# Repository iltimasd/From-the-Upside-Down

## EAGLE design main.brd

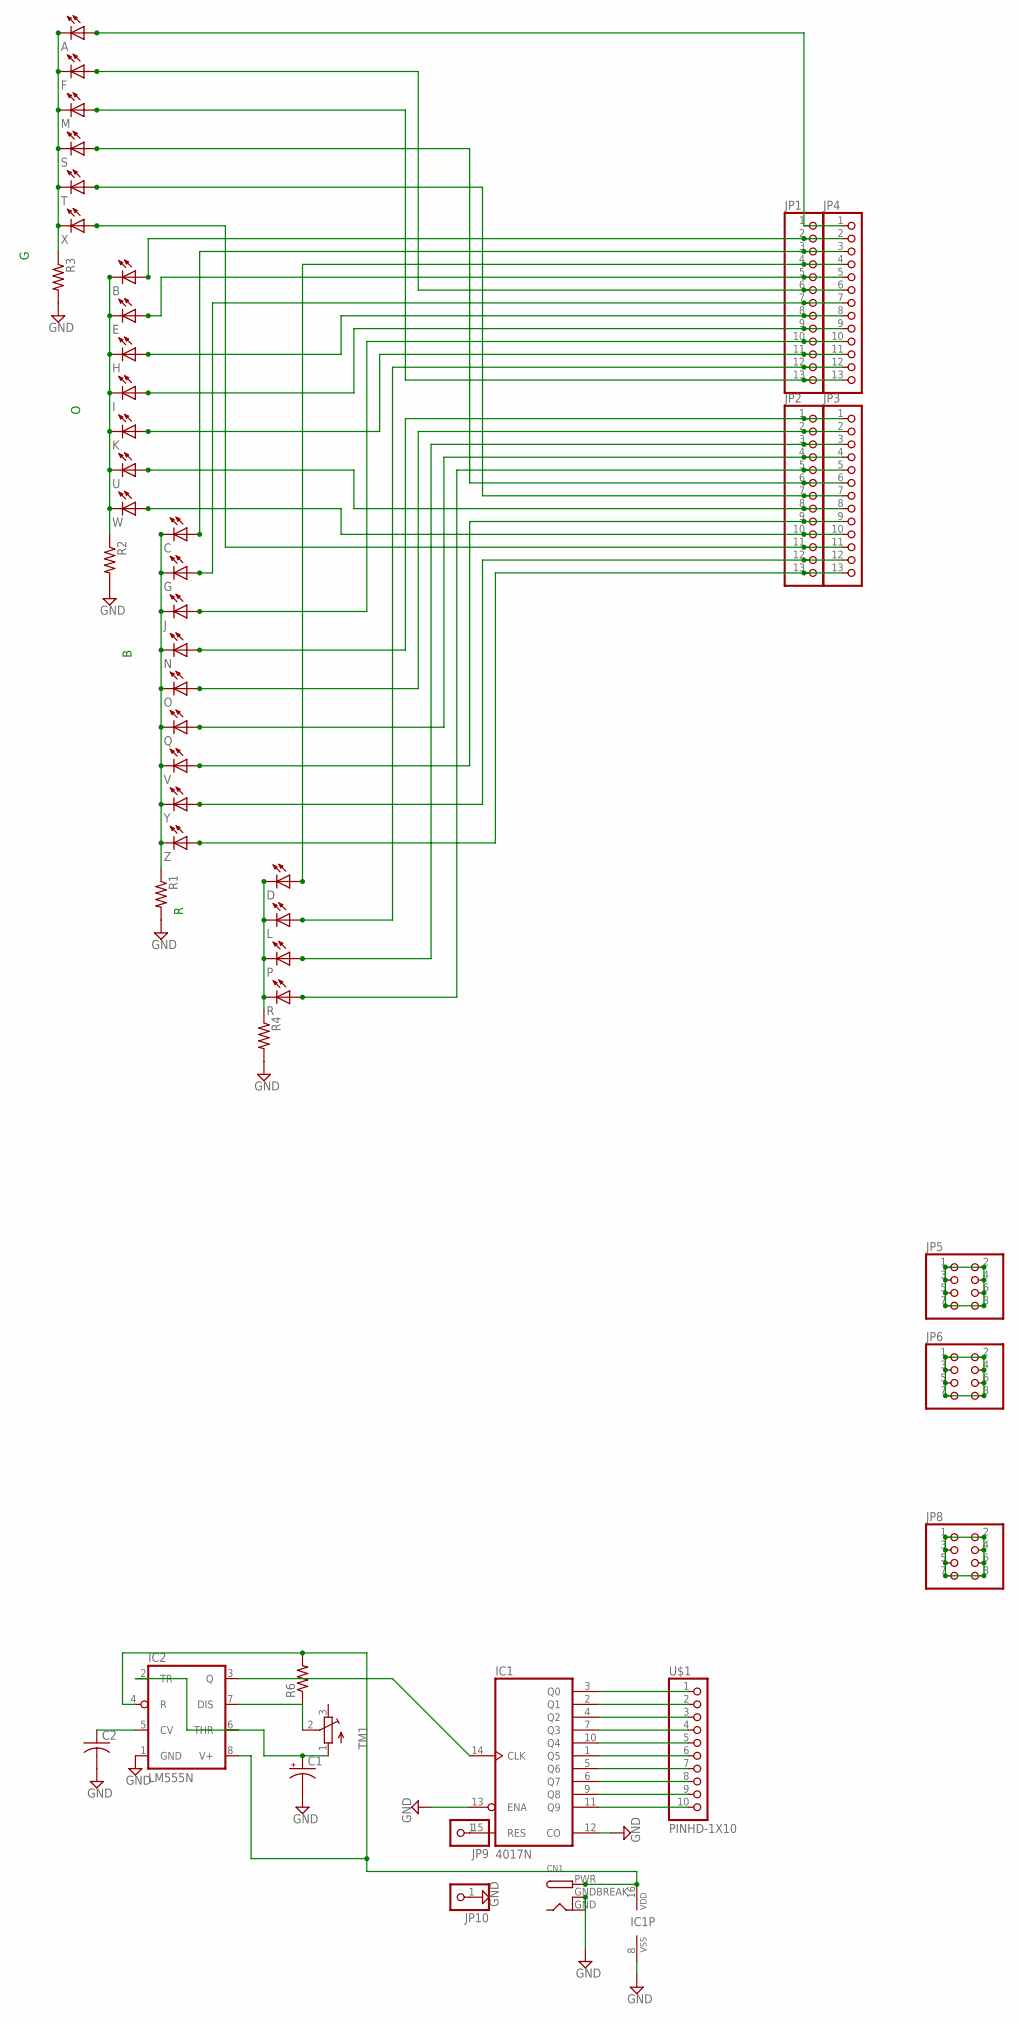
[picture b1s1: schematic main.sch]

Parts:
A: LED3MM
B: LED3MM
C: LED3MM
C1: CPOL-USE3.5-10; E3,5-10
C2: C-US025-024X044; C025-024X044
CN1: DCBARRELPTH; DCJACK_2MM_PTH
D: LED3MM
E: LED3MM
F: LED3MM
G: LED3MM
H: LED3MM
I: LED3MM
IC1: 4017N; DIL16
IC2: LM555N; DIL08
J: LED3MM
JP1, JP2, JP3, JP4: PINHD-1X13; 1X13
JP5, JP6, JP8: PINHD-2X4; 2X04
JP9, JP10: PINHD-1X1; 1X01
K: LED3MM
L: LED3MM
M: LED3MM
N: LED3MM
O: LED3MM
P: LED3MM
Q: LED3MM
R: LED3MM
R1, R2, R3, R4, R6: R-US_0207/7; 0207/7
S: LED3MM
T: LED3MM
TM1: TRIMPOT3386; TRIM-3386
U: LED3MM
U$1: PINHD-1X10; 1X10-BIG
V: LED3MM
W: LED3MM
X: LED3MM
Y: LED3MM
Z: LED3MM

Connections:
A: A.K (C), F.K (C), M.K (C), R3.1, S.K (C), T.K (C), X.K (C)
GND: C1.-, C2.2, CN1.GND, CN1.GNDBREAK, IC1.8 (VSS), IC1.12 (CO), IC1.13 (ENA), IC2.1 (GND), JP10.1, R1.2, R2.2, R3.2, R4.2
unnamed: B.K (C), E.K (C), H.K (C), I.K (C), K.K (C), R2.1, U.K (C), W.K (C)
unnamed: D.K (C), L.K (C), P.K (C), R.K (C), R4.1
unnamed: IC1.3 (Q0), U$1.1
unnamed: IC1.2 (Q1), U$1.2
unnamed: IC1.4 (Q2), U$1.3
unnamed: IC1.7 (Q3), U$1.4
unnamed: IC1.10 (Q4), U$1.5
unnamed: IC1.1 (Q5), U$1.6
unnamed: IC1.5 (Q6), U$1.7
unnamed: IC1.6 (Q7), U$1.8
unnamed: IC1.9 (Q8), U$1.9
unnamed: IC1.11 (Q9), U$1.10
unnamed: CN1.PWR, IC1.16 (VDD), IC2.4 (R), IC2.8 (V+), R6.2
unnamed: A.A, JP1.1, JP4.1
unnamed: B.A, JP1.2, JP4.2
unnamed: JP1.12, JP4.12, L.A
unnamed: F.A, JP1.6, JP4.6
unnamed: IC1.15 (RES), JP9.1
unnamed: G.A, JP1.7, JP4.7
unnamed: JP2.2, JP3.2, O.A
unnamed: JP1.11, JP4.11, K.A
unnamed: C1.+, IC2.2 (TR), IC2.6 (THR), TM1.1 (A)
unnamed: JP2.3, JP3.3, P.A
unnamed: JP2.12, JP3.12, Y.A
unnamed: JP2.13, JP3.13, Z.A
unnamed: JP5.1, JP5.2, JP5.3, JP5.4, JP5.5, JP5.6, JP5.7, JP5.8
unnamed: JP6.1, JP6.2, JP6.3, JP6.4, JP6.5, JP6.6, JP6.7, JP6.8
unnamed: JP8.1, JP8.2, JP8.3, JP8.4, JP8.5, JP8.6, JP8.7, JP8.8
unnamed: J.A, JP1.10, JP4.10
unnamed: IC2.7 (DIS), R6.1, TM1.2 (S)
unnamed: D.A, JP1.4, JP4.4
unnamed: C2.1, IC2.5 (CV)
unnamed: IC1.14 (CLK), IC2.3 (Q)
unnamed: I.A, JP1.9, JP4.9
unnamed: JP1.13, JP4.13, M.A
unnamed: JP2.1, JP3.1, N.A
unnamed: JP2.4, JP3.4, Q.A
unnamed: JP2.6, JP3.6, S.A
unnamed: JP2.7, JP3.7, T.A
unnamed: JP2.8, JP3.8, U.A
unnamed: JP2.9, JP3.9, V.A
unnamed: JP2.10, JP3.10, W.A
unnamed: JP2.11, JP3.11, X.A
unnamed: JP2.5, JP3.5, R.A
unnamed: H.A, JP1.8, JP4.8
unnamed: E.A, JP1.5, JP4.5
unnamed: C.A, JP1.3, JP4.3
RGND: C.K (C), G.K (C), J.K (C), N.K (C), O.K (C), Q.K (C), R1.1, V.K (C), Y.K (C), Z.K (C)

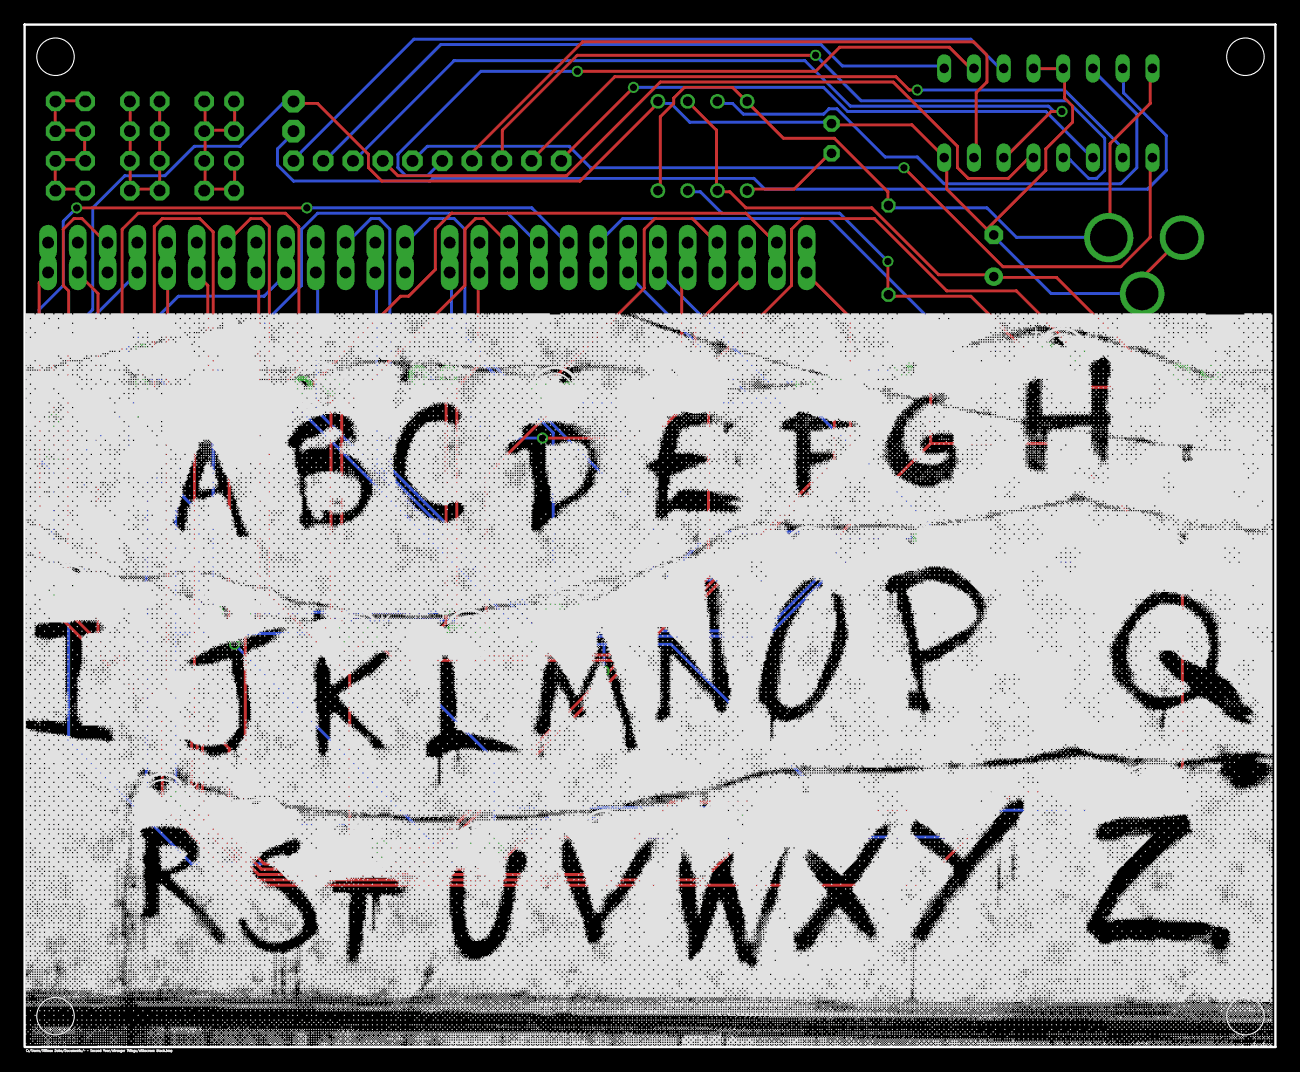
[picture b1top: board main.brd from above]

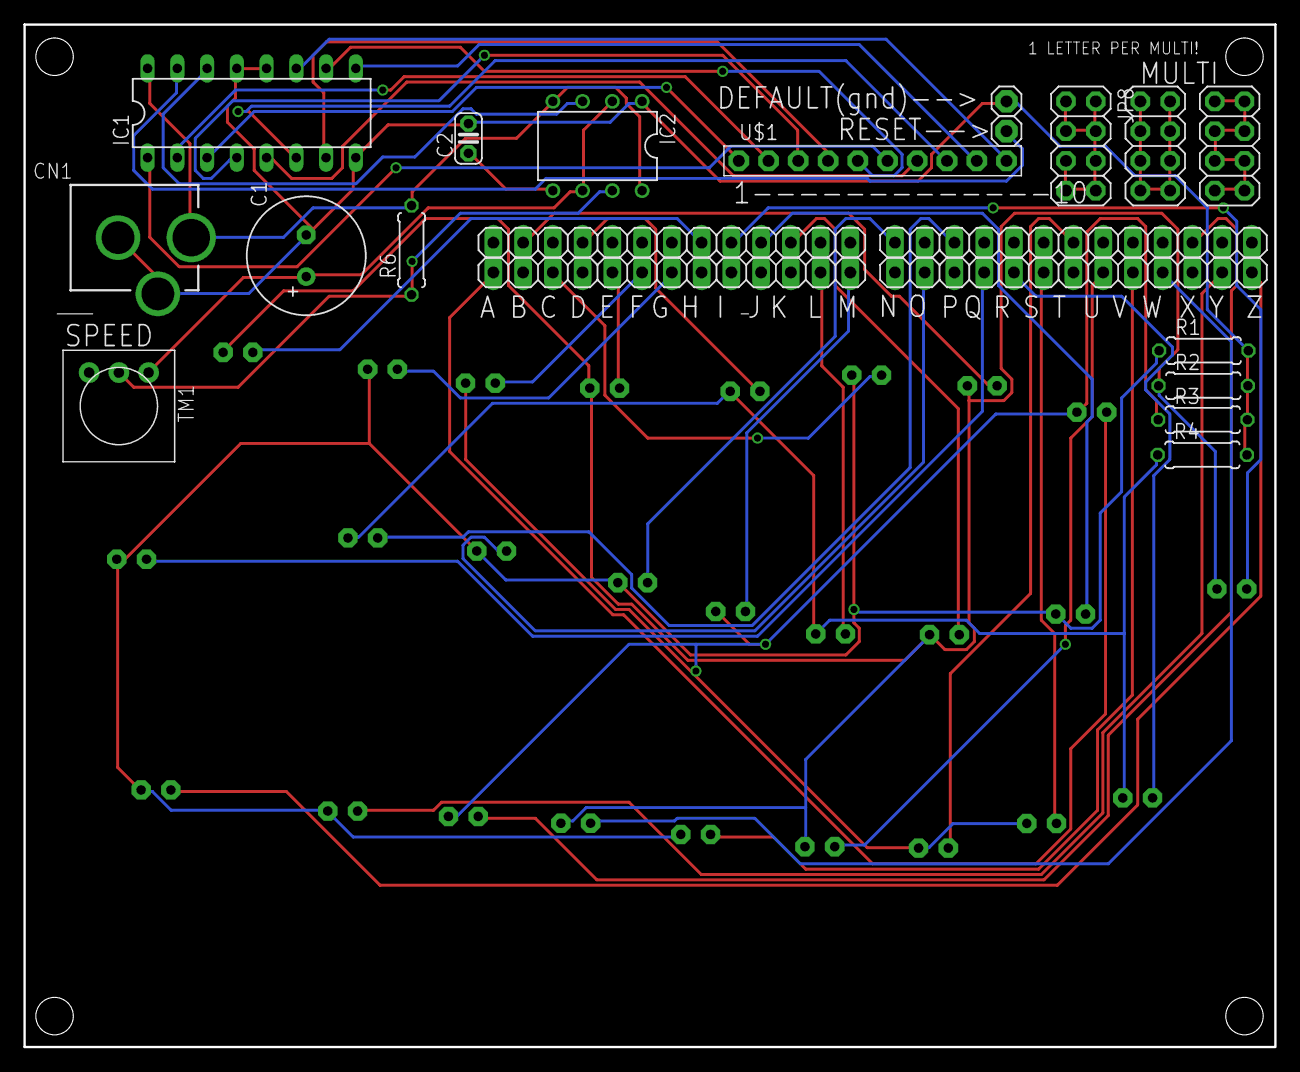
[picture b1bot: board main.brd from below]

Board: 2 copper layers, 106.8 x 87.3 mm, 47 parts (21 on the bottom side), 50 nets.

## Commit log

2017-01-13 File dump
2017-07-31 Added license
